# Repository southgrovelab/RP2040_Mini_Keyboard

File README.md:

# RP2040 Mini Keyboard

A tiny four-key USB keyboard in a USB stick form factor, built around the RP2040 and running [QMK](https://qmk.fm/) firmware.

## Version

Version 3.0, for PCB Rev C (1792604589).

## How it works

The keyboard has four keys and two modes. The LED shows which mode is active.

| Key | Normal mode, short press | Normal mode, long press (0.5 s) | Arrow mode (LED on) |
| --- | --- | --- | --- |
| Key 1 | Esc | – | ← Left |
| Key 2 | Tab | – | ↑ Up |
| Key 3 | Enter | – | ↓ Down |
| Key 4 | F1 | Ctrl+Alt+Del | → Right |

- **Switch mode:** press Key 1 and Key 4 at the same time. Press them together again to go back.
- **Long press on Key 4:** Ctrl+Alt+Del is sent once the key has been held for 0.5 seconds. A short press sends F1.
- **Bootloader:** hold Key 1 while plugging the keyboard in. It shows up as the USB drive `RPI-RP2`, ready for new firmware.

The full user manual, in English and Swedish, is in [Manual](Manual/).

## Repository contents

| Folder | Contents |
| --- | --- |
| [Firmware/rppk](Firmware/rppk) | QMK keyboard definition and default keymap |
| [KiCad](KiCad) | Schematic, PCB layout, project file (KiCad 10) and 3D models |
| [Production](Production) | Gerber and drill files (zip), bill of materials (`bom.csv`) and component positions (`.pos`) |
| [3D](3D) | Print-ready enclosure for Bambu Lab (.3mf) |
| [Manual](Manual) | User manual (Markdown and PDF) |
| [Images](Images) | Product pictures |

## Hardware

| Part | Component |
| --- | --- |
| MCU | Raspberry Pi RP2040 |
| Flash | Winbond W25Q16JVUXIQ, 2 MB (USON-8, 2 × 3 mm) |
| Crystal | Abracon ABM8-272-T3, 12 MHz |
| 3.3 V regulator | Microchip MCP1700T-3302E/MAY |
| USB ESD protection | ST USBLC6-2SC6 |
| USB connector | Molex 48037-2200, USB-A plug |
| Keys | Alps SKHU tactile switches |
| LED | Rohm SML-D12V8WT86 |

GPIO assignment:

| Function | GPIO |
| --- | --- |
| Key 1 (Esc) | GP22 |
| Key 2 (Tab) | GP23 |
| Key 3 (Enter) | GP19 |
| Key 4 (F1 / Ctrl+Alt+Del) | GP20 |
| Arrow mode LED | GP18 |

## Building the firmware

The firmware is built with QMK. The steps below are for Linux; see the [QMK getting started guide](https://docs.qmk.fm/newbs_getting_started) for Windows and macOS.

### 1. Install QMK

On Debian or Ubuntu:

```bash
sudo apt install pipx git dos2unix
pipx install qmk
pipx ensurepath
```

Open a new terminal, then run:

```bash
qmk setup
```

Answer yes to the questions. This downloads QMK to `~/qmk_firmware` and installs the compiler.

### 2. Add the keyboard to QMK

From the root of this repository:

```bash
cp -r Firmware/rppk ~/qmk_firmware/keyboards/
```

### 3. Compile

```bash
qmk compile -kb rppk -km default
```

The finished firmware is saved as `~/qmk_firmware/rppk_default.uf2`.

## Flashing

1. Put the keyboard in bootloader mode:
   - A new board with empty flash starts in bootloader mode by itself.
   - Otherwise, hold Key 1 while plugging the keyboard in.
2. The keyboard shows up as a USB drive called `RPI-RP2`.
3. Copy `rppk_default.uf2` to the drive. The keyboard restarts on its own and is ready to use.

```bash
cp ~/qmk_firmware/rppk_default.uf2 /media/$USER/RPI-RP2/
```

## Customizing

All settings are in `Firmware/rppk/keymaps/default/`. Recompile and flash after a change.

| What to change | Where |
| --- | --- |
| Key functions, for example F1 to F2 | `keymap.c`: change `KC_F1` to `KC_F2` in `#define F1_CAD LT(0, KC_F1)` |
| Long press time (default 500 ms) | `config.h`: `TAPPING_TERM` |
| How close together Key 1 and Key 4 must be pressed (default 50 ms) | `config.h`: `COMBO_TERM` |

Key names are listed in the [QMK keycode reference](https://docs.qmk.fm/keycodes).

## Bill of Materials (3D)

To assemble the enclosure, you will need the following hardware in addition to the 3D-printed parts:

| Qty | Part | Specification | Notes |
| :--- | :--- | :--- | :--- |
| 4 | Screw | M2 x 8 mm | Socket head or pan head |
| 4 | Nut | M2 | Standard hex nut |

The spacers are necessary and must be placed between the lid and the PCB.

## License

| Part | License | File |
| --- | --- | --- |
| Firmware (`Firmware/`) | GPL-2.0-or-later | [Firmware/LICENSE](Firmware/LICENSE) |
| Hardware: KiCad files, Gerbers, enclosure (`KiCad/`, `Production/`, `3D/`) | CERN-OHL-S-2.0 | [LICENSE](LICENSE) |

If you make and distribute a modified version of the hardware, CERN-OHL-S-2.0 requires that you share your modified design files under the same licence.

## Author

Niclas Söderlund, Pickels 3D LAB, 2026

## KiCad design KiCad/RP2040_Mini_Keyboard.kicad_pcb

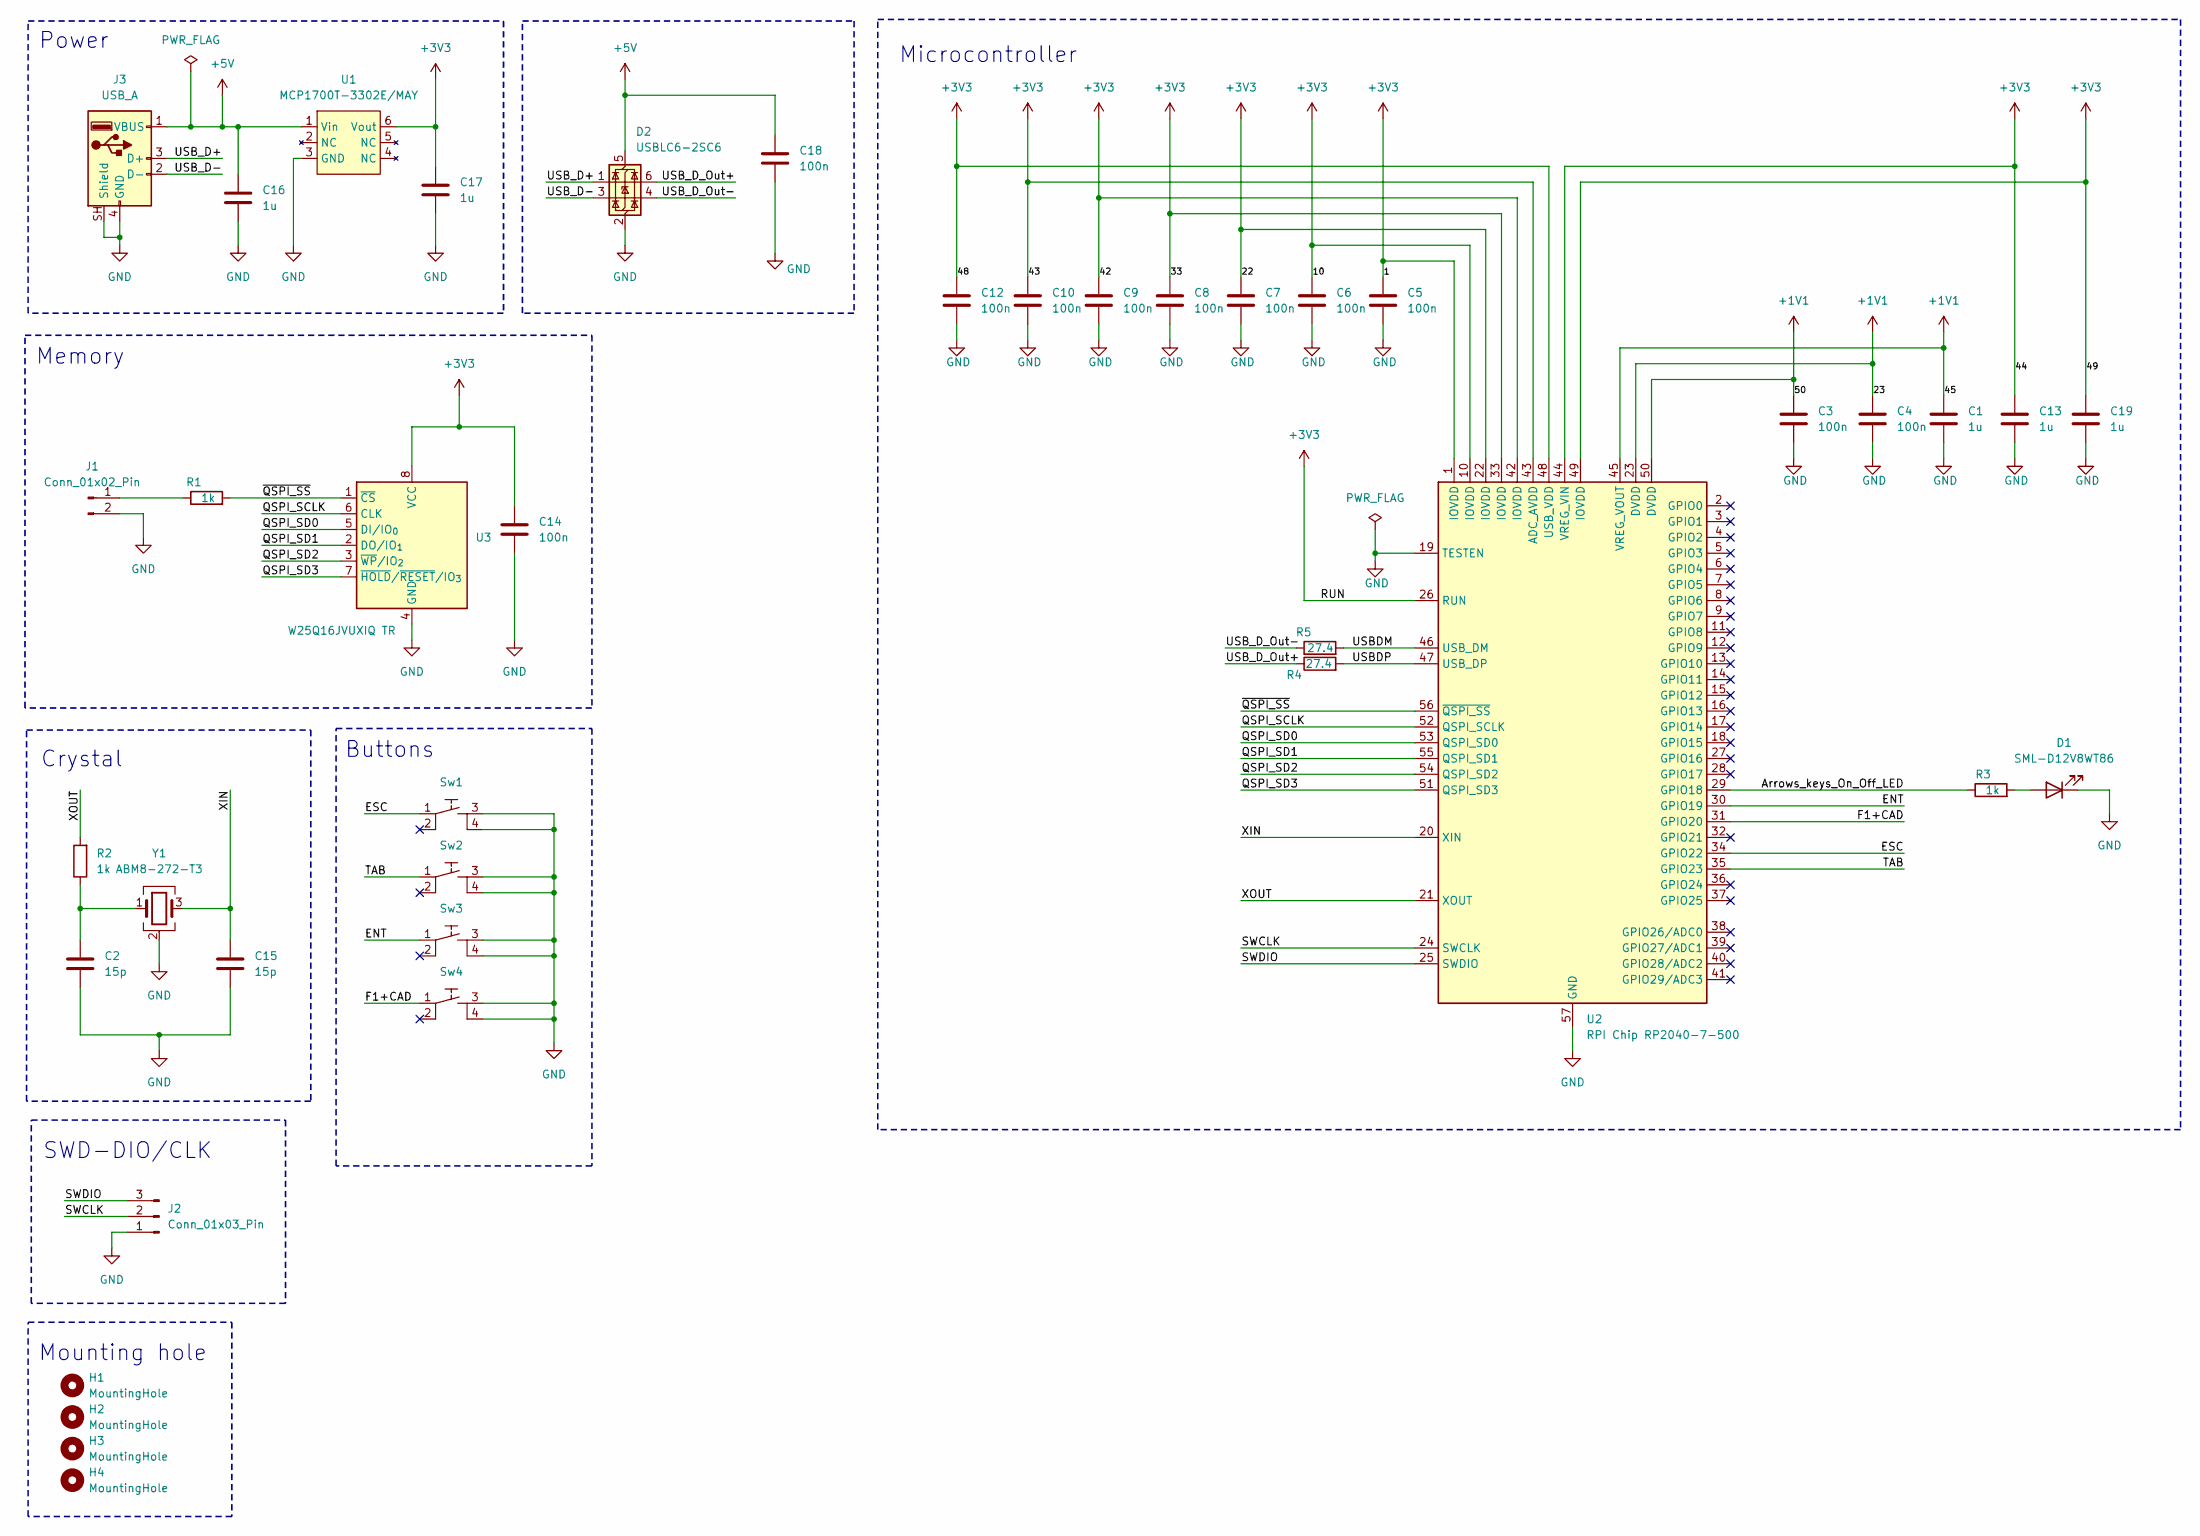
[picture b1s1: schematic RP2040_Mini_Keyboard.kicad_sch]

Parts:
C1, C13, C16, C17, C19: 1u; C_0402_1005Metric; MPN GXT155R61A105KE01D
C2, C15: 15p; C_0402_1005Metric; MPN CQ0100JRNPO8BN150
C3, C4, C5, C6, C7, C8, C9, C10, C12, C14, C18: 100n; C_0402_1005Metric; MPN C0402C104M9PACTU
D1: SML-D12V8WT86; LED_0603_1608Metric; MPN SML-D12V8WT86
D2: USBLC6-2SC6; SOT-23-6; MPN USBLC6-2SC6
H1, H2, H3, H4: MountingHole; Mounting_Hole_2mm_M2
J1: Conn_01x02_Pin; SolderJumper-2_P1.3mm_Open_RoundedPad1.0x1.5mm
J2: Conn_01x03_Pin; SolderJumper-3_P1.3mm_Open_RoundedPad1.0x1.5mm
J3: USB_A; USB_A_Molex_48037-2200_Horizontal
R1, R2: 1k; R_0402_1005Metric; MPN CR0402-JW-102GLF
R3: 1k; R_0603_1608Metric; MPN CR0603-FX-1001ELF
R4, R5: 27.4; R_0402_1005Metric; MPN AC0402FR-0727R4L
Sw1, Sw2, Sw3, Sw4: SKHU_; MPN SKHUALE010
U1: MCP1700T-3302E/MAY; DFN-6-1EP_2x2mm_P0.65mm_EP1x1.6mm; MPN MCP1700T-3302E/MAY
U2: RPI Chip RP2040-7-500; QFN-56-1EP_7x7mm_P0.4mm_EP3.2x3.2mm; MPN RPI Chip RP2040-7-500
U3: W25Q16JVUXIQ TR; Winbond_USON-8-1EP_3x2mm_P0.5mm_EP0.2x1.6mm; MPN W25Q16JVUXIQ TR
Y1: ABM8-272-T3; ABM8272T3; MPN ABM8-272-T3

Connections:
+1V1: C1.1, C3.1, C4.1, U2.23 (DVDD), U2.45 (VREG_VOUT), U2.50 (DVDD)
+3V3: C5.1, C6.1, C7.1, C8.1, C9.1, C10.1, C12.1, C13.1, C14.1, C17.1, C19.1, U1.6 (Vout), U2.1 (IOVDD), U2.10 (IOVDD), U2.22 (IOVDD), U2.26 (RUN), U2.33 (IOVDD), U2.42 (IOVDD), U2.43 (ADC_AVDD), U2.44 (VREG_VIN), U2.48 (USB_VDD), U2.49 (IOVDD), U3.8 (VCC)
+5V: C16.1, C18.1, D2.5 (VBUS), J3.1 (VBUS), U1.1 (Vin)
/Arrows_keys_On_Off_LED: R3.1, U2.29 (GPIO18)
/ENT: Sw3.1, U2.30 (GPIO19)
/ESC: Sw1.1, U2.34 (GPIO22)
/F1+CAD: Sw4.1, U2.31 (GPIO20)
/QSPI_SCLK: U2.52 (QSPI_SCLK), U3.6 (CLK)
/QSPI_SD0: U2.53 (QSPI_SD0), U3.5 (DI/IO_{0})
/QSPI_SD1: U2.55 (QSPI_SD1), U3.2 (DO/IO_{1})
/QSPI_SD2: U2.54 (QSPI_SD2), U3.3 (~WP/IO_{2})
/QSPI_SD3: U2.51 (QSPI_SD3), U3.7 (~HOLD/~RESET/IO_{3})
/SWCLK: J2.2, U2.24 (SWCLK)
/SWDIO: J2.3, U2.25 (SWDIO)
/TAB: Sw2.1, U2.35 (GPIO23)
/USBDM: R5.2, U2.46 (USB_DM)
/USBDP: R4.2, U2.47 (USB_DP)
/USB_D+: D2.1 (I/O1), J3.3 (D+)
/USB_D-: D2.3 (I/O2), J3.2 (D-)
/USB_D_Out+: D2.6 (I/O1), R4.1
/USB_D_Out-: D2.4 (I/O2), R5.1
/XIN: C15.1, U2.20 (XIN), Y1.3
/XOUT: R2.2, U2.21 (XOUT)
/~QSPI_SS: R1.2, U2.56 (~QSPI_SS), U3.1 (~CS)
GND: C1.2, C2.2, C3.2, C4.2, C5.2, C6.2, C7.2, C8.2, C9.2, C10.2, C12.2, C13.2, C14.2, C15.2, C16.2, C17.2, C18.2, C19.2, D1.1 (K), D2.2 (GND), J1.2, J2.1, J3.4 (GND), J3.SH (Shield), Sw1.3, Sw1.4, Sw2.3, Sw2.4, Sw3.3, Sw3.4, Sw4.3, Sw4.4, U1.3 (GND), U1.7 (GND), U2.19 (TESTEN), U2.57 (GND), U3.4 (GND), U3.9, Y1.2 (G), Y1.4 (G)
unnamed: C2.1, R2.1, Y1.1
unnamed: D1.2 (A), R3.2
unnamed: J1.1, R1.1

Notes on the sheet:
Memory
Mounting hole
Microcontroller
Crystal
Buttons
SWD-DIO/CLK
Power

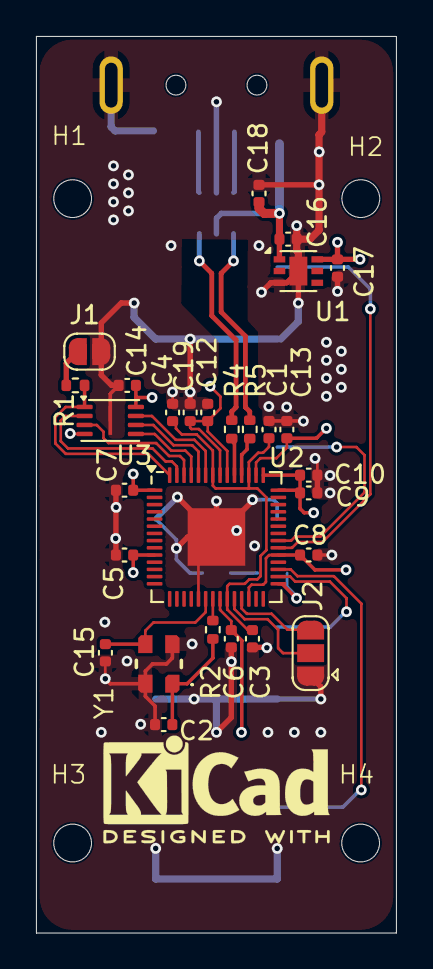
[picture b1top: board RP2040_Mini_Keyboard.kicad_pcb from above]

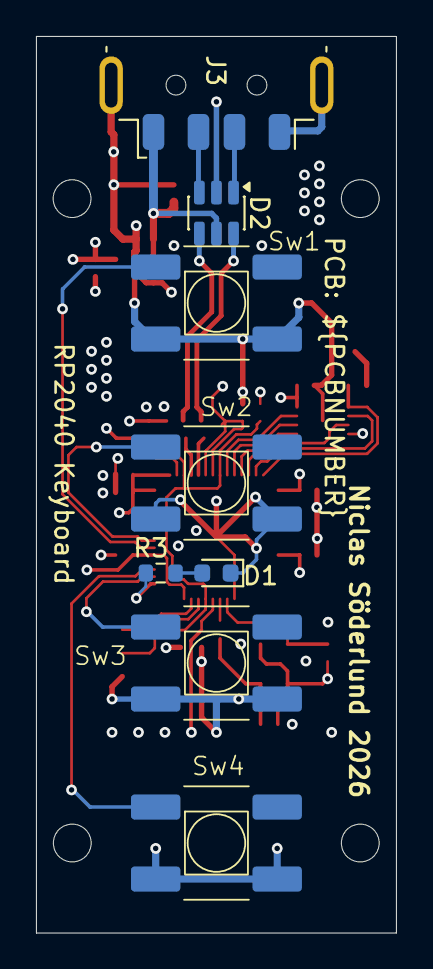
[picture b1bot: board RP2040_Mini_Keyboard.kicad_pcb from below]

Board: 4 copper layers, 20.0 x 49.8 mm, 40 parts (8 on the bottom side), 28 nets.

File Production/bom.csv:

Designator,Footprint,Quantity,Value,MPN
"C1, C13, C16, C17, C19",0402,5,1u,GXT155R61A105KE01D
"C10, C12, C14, C18, C3, C4, C5, C6, C7, C8, C9",0402,11,100n,C0402C104M9PACTU
"C15, C2",0402,2,15p,CQ0100JRNPO8BN150
D1,0603,1,SML-D12V8WT86,SML-D12V8WT86
D2,SOT-23-6,1,USBLC6-2SC6,USBLC6-2SC6
J1,SolderJumper-2_P1.3mm_Open_RoundedPad1.0x1.5mm,0,DNP (solder jumper),
J2,SolderJumper-3_P1.3mm_Open_RoundedPad1.0x1.5mm,0,DNP (solder jumper),
J3,USB_A_Molex_48037-2200_Horizontal,1,USB_A,48037-2200
"R1, R2",0402,2,1k,CR0402-JW-102GLF
R3,0603,1,1k,CR0603-FX-1001ELF
"R4, R5",0402,2,27.4,AC0402FR-0727R4L
"SW1, SW2, SW3, SW4",SKHU_,4,~,SKHUALE010
U1,DFN-6-1EP_2x2mm_P0.65mm_EP1x1.6mm,1,MCP1700T-3302E/MAY,MCP1700T-3302E/MAY
U2,QFN-56-1EP_7x7mm_P0.4mm_EP3.2x3.2mm,1,RPI Chip RP2040-7-500,RPI Chip RP2040-7-500
U3,Winbond_USON-8-1EP_3x2mm_P0.5mm_EP0.2x1.6mm,1,W25Q16JVUXIQ TR,W25Q16JVUXIQ TR
Y1,ABM8272T3,1,ABM8-272-T3,ABM8-272-T3
